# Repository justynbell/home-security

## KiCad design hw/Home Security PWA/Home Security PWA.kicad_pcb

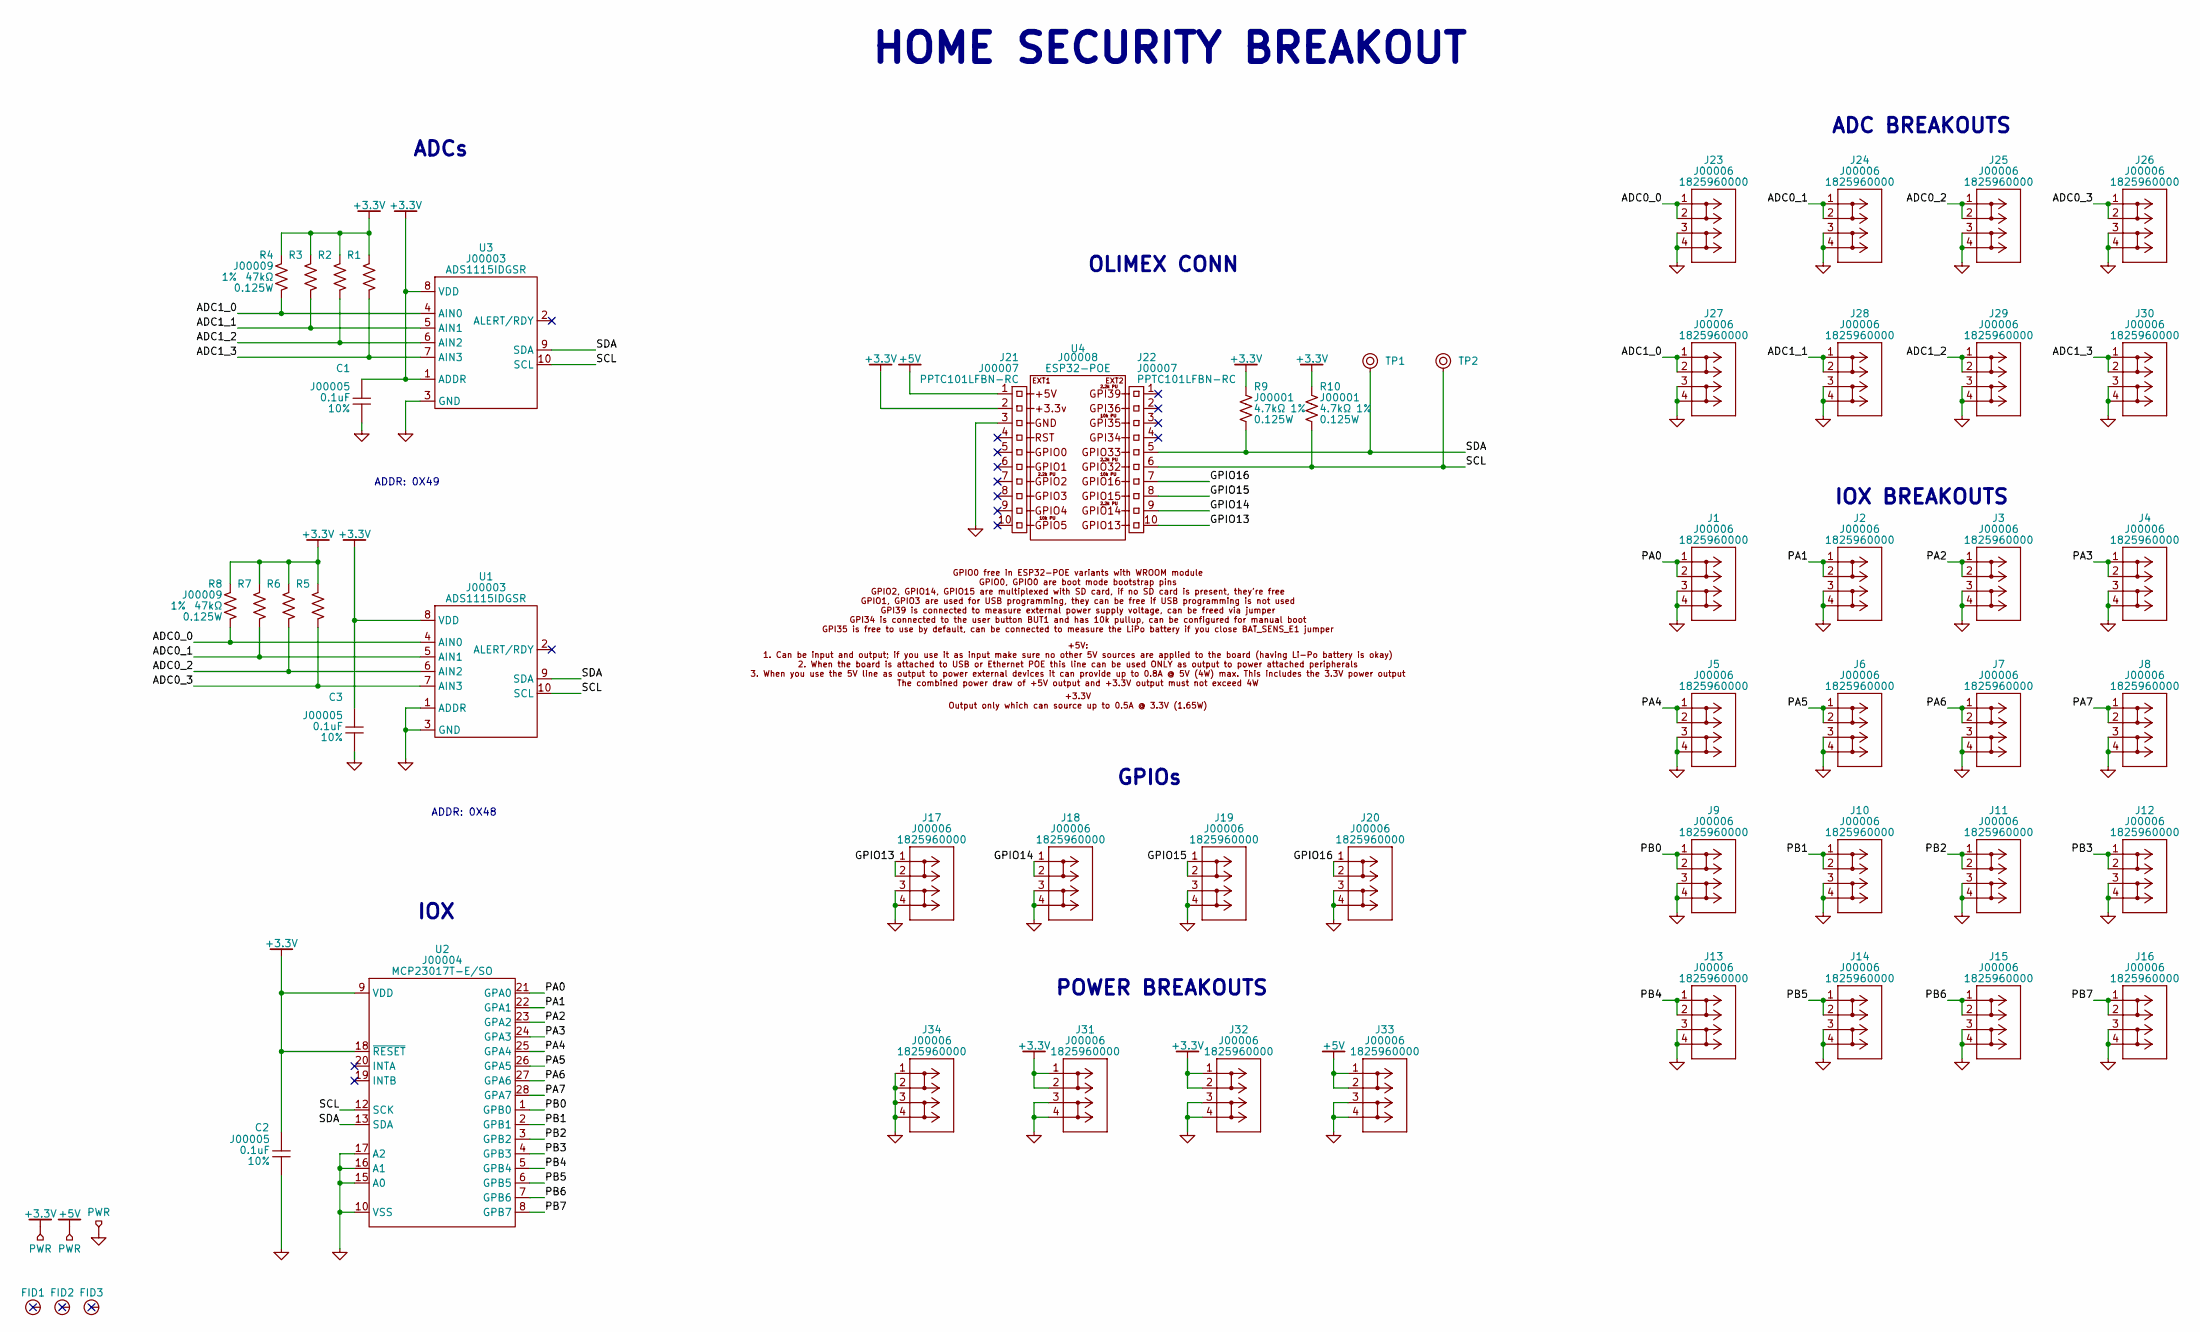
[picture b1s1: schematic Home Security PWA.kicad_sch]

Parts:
C1, C2, C3: J00005; CAPC201X125X100L50M; Tolerance 10%; Voltage 25V; MPN_1 KGM21NR71E104KT
FID1, FID2, FID3: FIDUCIAL_1MM
J1, J2, J3, J4, J5, J6, J7, J8, J9, J10, J11, J12, J13, J14, J15, J16, J17, J18, J19, J20, J23, J24, J25, J26, J27, J28, J29, J30, J31, J32, J33, J34: J00006; Voltage 300V; MPN_1 1825960000
J21, J22: J00007; RHDRV10W64P254_10X1_2590X254H850; Voltage 250V; MPN_1 PPTC101LFBN-RC
R1, R2, R3, R4, R5, R6, R7, R8: J00009; RESC2012X60M; Tolerance 1%; Voltage 150V; MPN_1 CRCW080547K0FKEAC
R9, R10: J00001; RESC2012X60M; Tolerance 1%; Voltage 150V; MPN_1 CRCW08054K70FKEAC
TP1, TP2: TESTPOINT_TH_1MMD
U1, U3: J00003; SOP10P50_300X490X110L55X22M; Voltage 5.5V; Voltage Min 2V; MPN_1 ADS1115IDGSR
U2: J00004; SOIC127P1030X265-28M; Voltage 5.5V; Voltage Min 1.8V; MPN_1 MCP23017T-E/SO
U4: J00008; MPN_1 ESP32-POE

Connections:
+3.3V: C1.1, C2.1, C3.1, J21.2, J31.1, J31.2, J32.1, J32.2, R1.2, R2.2, R3.2, R4.2, R5.2, R6.2, R7.2, R8.2, R9.2, R10.2, U1.8 (VDD), U2.9 (VDD), U2.18 (~RESET), U3.1 (ADDR), U3.8 (VDD)
+5V: J21.1, J33.1, J33.2
/ADC0_0: J23.1, J23.2, R8.1, U1.4 (AIN0)
/ADC0_1: J24.1, J24.2, R7.1, U1.5 (AIN1)
/ADC0_2: J25.1, J25.2, R6.1, U1.6 (AIN2)
/ADC0_3: J26.1, J26.2, R5.1, U1.7 (AIN3)
/ADC1_0: J27.1, J27.2, R4.1, U3.4 (AIN0)
/ADC1_1: J28.1, J28.2, R3.1, U3.5 (AIN1)
/ADC1_2: J29.1, J29.2, R2.1, U3.6 (AIN2)
/ADC1_3: J30.1, J30.2, R1.1, U3.7 (AIN3)
/GPIO13: J17.1, J17.2, J22.10
/GPIO14: J18.1, J18.2, J22.9
/GPIO15: J19.1, J19.2, J22.8
/GPIO16: J20.1, J20.2, J22.7
/PA0: J1.1, J1.2, U2.21 (GPA0)
/PA1: J2.1, J2.2, U2.22 (GPA1)
/PA2: J3.1, J3.2, U2.23 (GPA2)
/PA3: J4.1, J4.2, U2.24 (GPA3)
/PA4: J5.1, J5.2, U2.25 (GPA4)
/PA5: J6.1, J6.2, U2.26 (GPA5)
/PA6: J7.1, J7.2, U2.27 (GPA6)
/PA7: J8.1, J8.2, U2.28 (GPA7)
/PB0: J9.1, J9.2, U2.1 (GPB0)
/PB1: J10.1, J10.2, U2.2 (GPB1)
/PB2: J11.1, J11.2, U2.3 (GPB2)
/PB3: J12.1, J12.2, U2.4 (GPB3)
/PB4: J13.1, J13.2, U2.5 (GPB4)
/PB5: J14.1, J14.2, U2.6 (GPB5)
/PB6: J15.1, J15.2, U2.7 (GPB6)
/PB7: J16.1, J16.2, U2.8 (GPB7)
/SCL: J22.6, R10.1, TP2.1, U1.10 (SCL), U2.12 (SCK), U3.10 (SCL)
/SDA: J22.5, R9.1, TP1.1, U1.9 (SDA), U2.13 (SDA), U3.9 (SDA)
GND: C1.2, C2.2, C3.2, J1.3, J1.4, J2.3, J2.4, J3.3, J3.4, J4.3, J4.4, J5.3, J5.4, J6.3, J6.4, J7.3, J7.4, J8.3, J8.4, J9.3, J9.4, J10.3, J10.4, J11.3, J11.4, J12.3, J12.4, J13.3, J13.4, J14.3, J14.4, J15.3, J15.4, J16.3, J16.4, J17.3, J17.4, J18.3, J18.4, J19.3, J19.4, J20.3, J20.4, J21.3, J23.3, J23.4, J24.3, J24.4, J25.3, J25.4, J26.3, J26.4, J27.3, J27.4, J28.3, J28.4, J29.3, J29.4, J30.3, J30.4, J31.3, J31.4, J32.3, J32.4, J33.3, J33.4, J34.1, J34.2, J34.3, J34.4, U1.1 (ADDR), U1.3 (GND), U2.10 (VSS), U2.15 (A0), U2.16 (A1), U2.17 (A2), U3.3 (GND)

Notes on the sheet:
GPIOs
HOME SECURITY BREAKOUT
ADC BREAKOUTS
IOX
ADDR: 0X48
IOX BREAKOUTS
OLIMEX CONN
POWER BREAKOUTS
ADCs
ADDR: 0X49

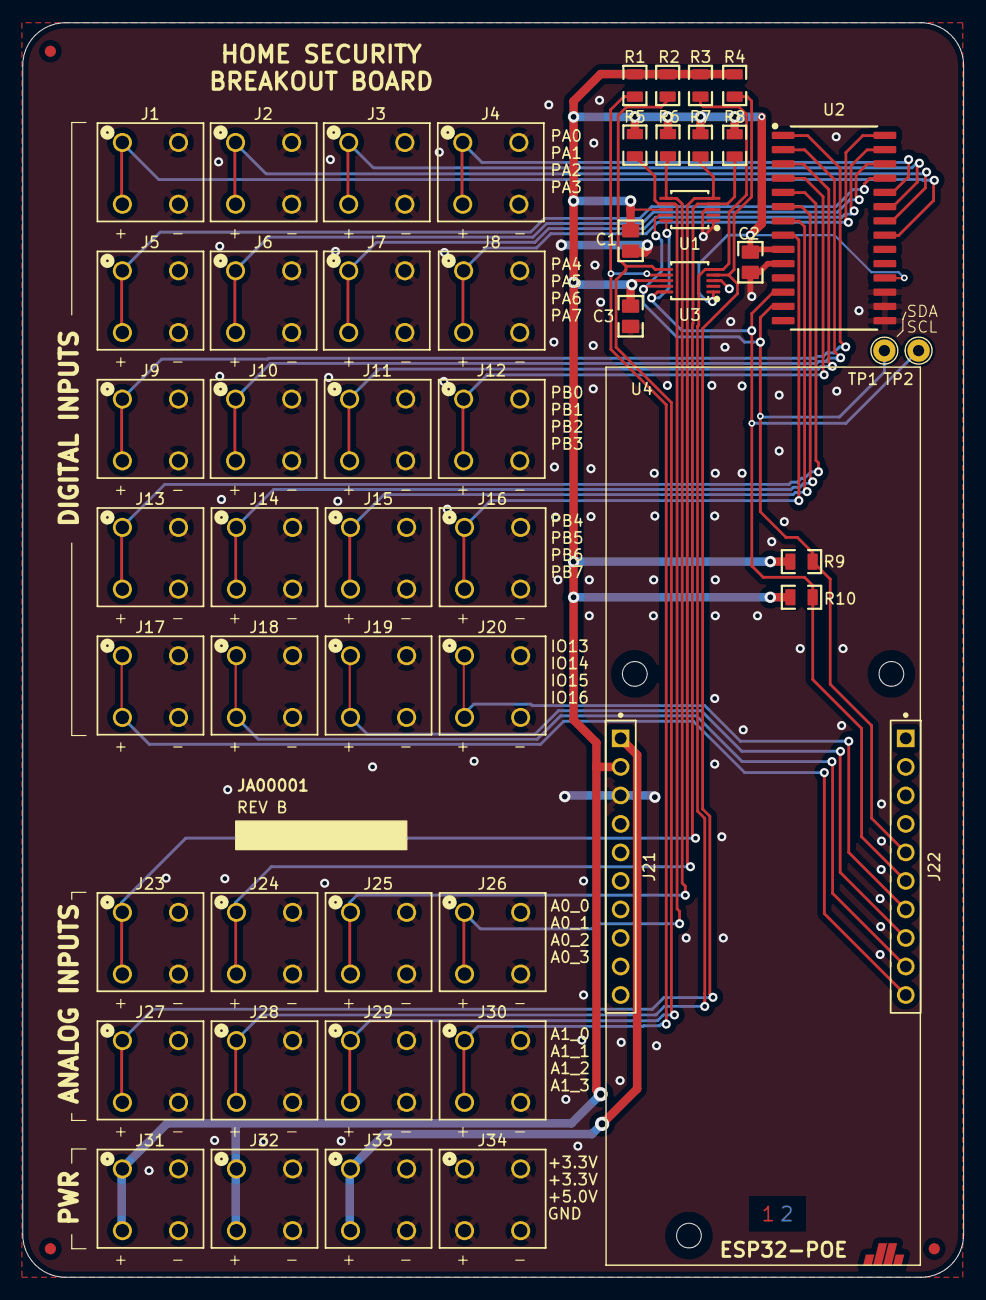
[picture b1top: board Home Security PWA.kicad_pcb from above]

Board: 2 copper layers, 83.8 x 111.8 mm, 56 parts (0 on the bottom side), 33 nets.

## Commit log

2026-03-03 Remove these "per project" components.
    Updates to Home Security with Inventree, new symbols, new schematics.
2026-03-05 More work.
2026-03-07 Using all custom symbols/footprints.
2026-03-09 Updates.
